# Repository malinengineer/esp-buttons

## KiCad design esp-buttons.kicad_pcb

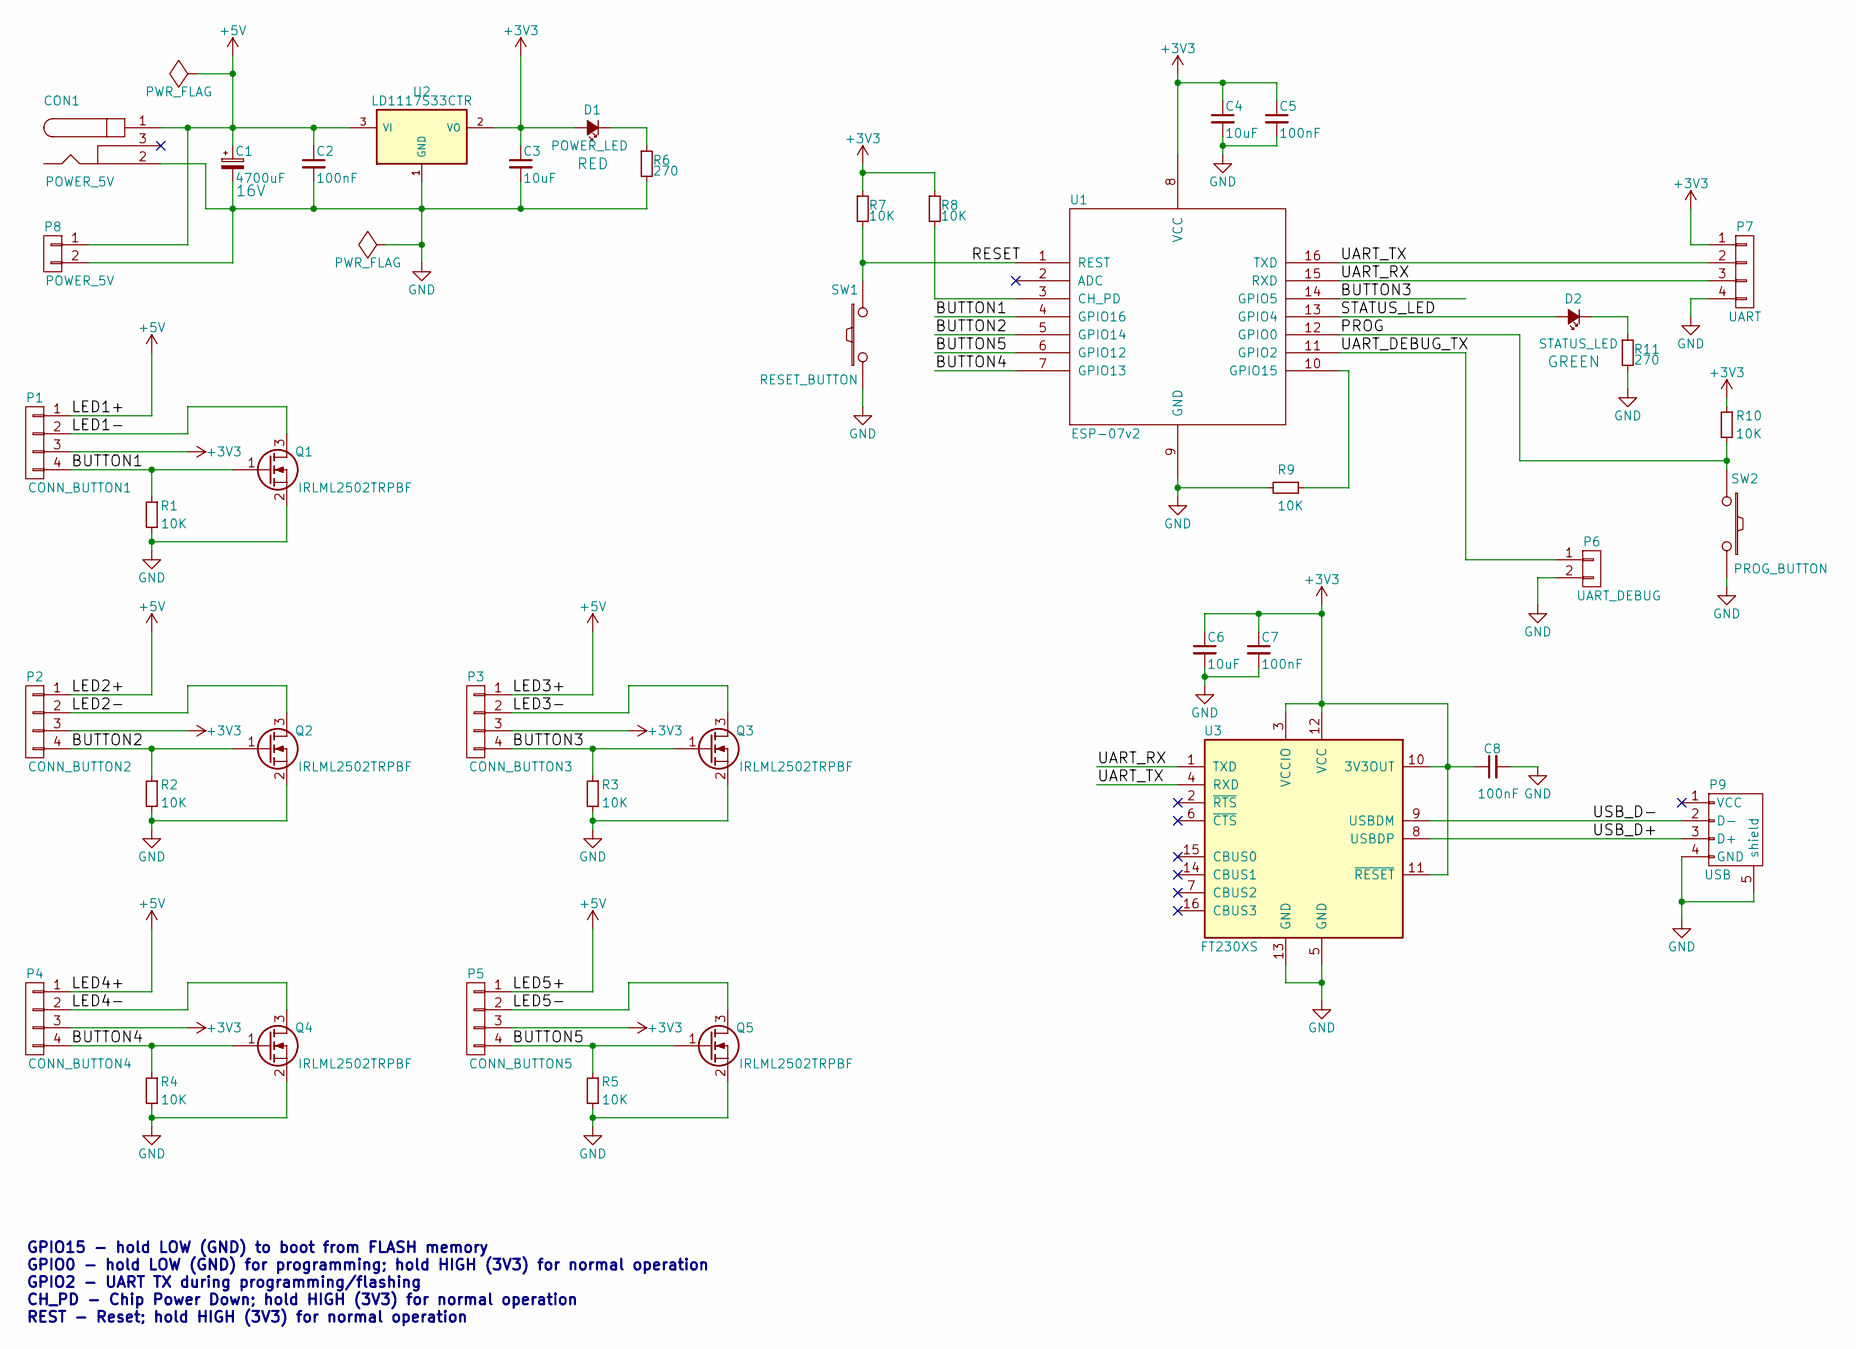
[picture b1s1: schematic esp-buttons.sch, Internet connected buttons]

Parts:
C1: 4700uF; C_Radial_D16_L25_P7.5; Voltage 16V
C2, C5, C7, C8: 100nF; C_1206_HandSoldering
C3, C4, C6: 10uF; C_1210_HandSoldering
CON1: POWER_5V; JACK_ALIM
D1: POWER_LED; LED_1206
D2: STATUS_LED; LED_1206
P1: CONN_BUTTON1; TerminalBlock_Pheonix_PT-3.5mm_4pol
P2: CONN_BUTTON2; TerminalBlock_Pheonix_PT-3.5mm_4pol
P3: CONN_BUTTON3; TerminalBlock_Pheonix_PT-3.5mm_4pol
P4: CONN_BUTTON4; TerminalBlock_Pheonix_PT-3.5mm_4pol
P5: CONN_BUTTON5; TerminalBlock_Pheonix_PT-3.5mm_4pol
P6: UART_DEBUG; Pin_Header_Straight_1x02
P7: UART; Pin_Header_Straight_1x04
P8: POWER_5V; TerminalBlock_Pheonix_PT-3.5mm_2pol
P9: USB; USB_B
Q1, Q2, Q3, Q4, Q5: IRLML2502TRPBF; SOT-23
R1, R2, R3, R4, R5, R7, R8, R9, R10: 10K; R_1206_HandSoldering
R6, R11: 270; R_1206_HandSoldering
SW1: RESET_BUTTON; SW_PUSH_6mm
SW2: PROG_BUTTON; SW_PUSH_6mm
U1: ESP-07v2
U2: LD1117S33CTR; TO-263-3Lead
U3: FT230XS; SSOP-16_3.9x4.9mm_Pitch0.635mm

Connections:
+3V3: C3.1, C4.1, C5.1, C6.1, C7.1, C8.1, D1.2 (A), P1.3, P2.3, P3.3, P4.3, P5.3, P7.1, R7.1, R8.1, R10.1, U1.8 (VCC), U2.2 (VO), U3.3 (VCCIO), U3.10 (3V3OUT), U3.11 (~RESET), U3.12 (VCC)
+5V: C1.1, C2.1, CON1.1, P1.1, P2.1, P3.1, P4.1, P5.1, P8.1, U2.3 (VI)
/BUTTON1: P1.4, Q1.1 (G), R1.1, U1.4 (GPIO16)
/BUTTON2: P2.4, Q2.1 (G), R2.1, U1.5 (GPIO14)
/BUTTON3: P3.4, Q3.1 (G), R3.1, U1.14 (GPIO5)
/BUTTON4: P4.4, Q4.1 (G), R4.1, U1.7 (GPIO13)
/BUTTON5: P5.4, Q5.1 (G), R5.1, U1.6 (GPIO12)
/LED1-: P1.2, Q1.3 (D)
/LED2-: P2.2, Q2.3 (D)
/LED3-: P3.2, Q3.3 (D)
/LED4-: P4.2, Q4.3 (D)
/LED5-: P5.2, Q5.3 (D)
/PROG: R10.2, SW2.1, U1.12 (GPIO0)
/RESET: R7.2, SW1.1, U1.1 (REST)
/STATUS_LED: D2.2 (A), U1.13 (GPIO4)
/UART_DEBUG_TX: P6.1, U1.11 (GPIO2)
/UART_RX: P7.3, U1.15 (RXD), U3.1 (TXD)
/UART_TX: P7.2, U1.16 (TXD), U3.4 (RXD)
/USB_D+: P9.3 (D+), U3.8 (USBDP)
/USB_D-: P9.2 (D-), U3.9 (USBDM)
GND: C1.2, C2.2, C3.2, C4.2, C5.2, C6.2, C7.2, C8.2, CON1.2, P6.2, P7.4, P8.2, P9.4 (GND), P9.5 (shield), Q1.2 (S), Q2.2 (S), Q3.2 (S), Q4.2 (S), Q5.2 (S), R1.2, R2.2, R3.2, R4.2, R5.2, R6.2, R9.2, R11.2, SW1.2, SW2.2, U1.9 (GND), U2.1 (GND), U2.4, U3.5 (GND), U3.13 (GND)
unnamed: D1.1 (K), R6.1
unnamed: D2.1 (K), R11.1
unnamed: R8.2, U1.3 (CH_PD)
unnamed: R9.1, U1.10 (GPIO15)

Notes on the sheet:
GPIO15 - hold LOW (GND) to boot from FLASH memory GPIO0 - hold LOW (GND) for programming; hold HIGH (3V3) for normal operation GPIO2 - UART TX during programming/flashing CH_PD - Chip Power Down; hold HIGH (3V3) for normal operation REST - Reset; hold HIGH (3V3) for normal operation

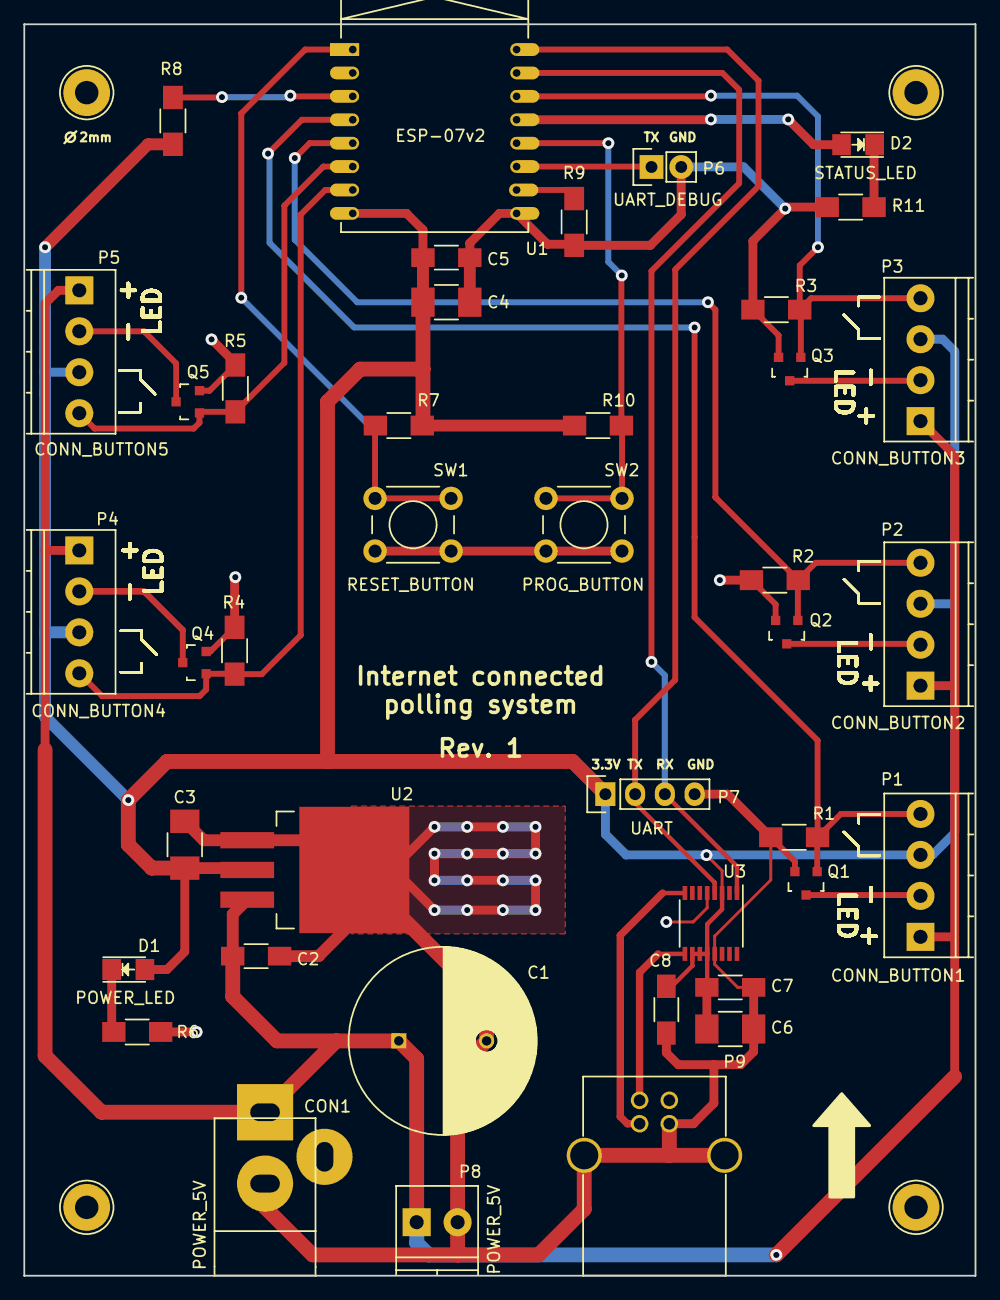
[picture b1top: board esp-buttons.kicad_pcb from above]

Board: 2 copper layers, 81.3 x 106.9 mm, 45 parts (0 on the bottom side), 25 nets.

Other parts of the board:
MT1, MT2, MT3, MT4: 1pin

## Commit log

2016-09-01 Removed one extra button circuitry
2016-09-01 Added .gitignore for KiCAD files
2016-09-01 Minor modification to the POWER LED. Removed from repository the files that are in .gitignore
2016-09-01 Temporary delete the libraries folder
2016-09-01 Re-added the 'kicad-ESP8266' libraries
2016-09-02 Added the ESP8266.pretty to the Footprint Library
2016-09-02 Changed the value of the LEDs' resistors to give aproximately 5 mA of current to the LEDs. Changed the package of the SMD regulator (LD1117ADT33TR) from SOT-223 to TO-263 (D-PAK) for increased power 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
2016-09-02 Added datasheets of some components used
2016-09-02 Removed the temporary buttons' circuits
2016-09-02 Added better circuit for BUTTON! & LED1
2016-09-02 Updated the .gitignore file
2016-09-02 Added the datasheet for the N-channel MOSFET 'IRLML2502TRPBF'
2016-09-02 Added the rest of the buttons' circuits. Annotated the schematic
2016-09-07 Added empty PCB document to the project
2016-09-07 Added image of ESP-12 pinout to the documentation
2016-09-25 Added datasheets for the USB Type B TH connectors and for a serial-to-USB IC (FT230X)
2016-09-25 Added circuit for USB-to-serial IC (FT230X). Added additional 5V power connector (terminal block connector)
2016-09-25 Added temporary footprints to the button's connectors and the buttons
2016-09-26 Annotated the rest of the schematic
2016-09-26 Fixed the footprint for the SW1 button
2016-09-26 Fixing most of the ERC errors (I guess)
2016-09-26 Assigning footprints to sch symbols for the ESP-07 & FT230XS
2016-09-26 Modified the switches sch symbols to have only 2 pin on the schematic
2016-09-26 Fixed a wrong connection
2016-09-26 Initial placement of components on the PCB and PCB settings. Fixed the 3D model for the ESP-07
2016-09-26 Added the 3 remaining mounting holes
2016-09-26 Added title text on top silkscreen
2016-09-28 Fixed some ERC warnings with the PWR_FLAG
2016-09-28 Rotated the PCB on a more logical orientation
2016-09-29 PCB settings. More component placement. Putting components' Value on the Silkscreen layer
2016-09-30 More component placement and track layout done
2016-10-04 More component placement and track layout done. Exchanged the connections of two buttons on the ESP's pins
2016-10-04 Track layout - part3
2016-10-11 Track layout - part4. Fixing some footprint's pads. Modifying the placment of the mounting holes. Added via stitches to the voltage regulator (U2)
2016-10-11 Added more datasheets to docs/
2016-10-13 Final layout. Added bottom GND pour. Added dimentions on 'Dwgs' layer.
2016-10-13 Updated the .gitignore file to ignore the 'output' folder
2016-10-13 Modifying the settings for plotting (Gerber)
